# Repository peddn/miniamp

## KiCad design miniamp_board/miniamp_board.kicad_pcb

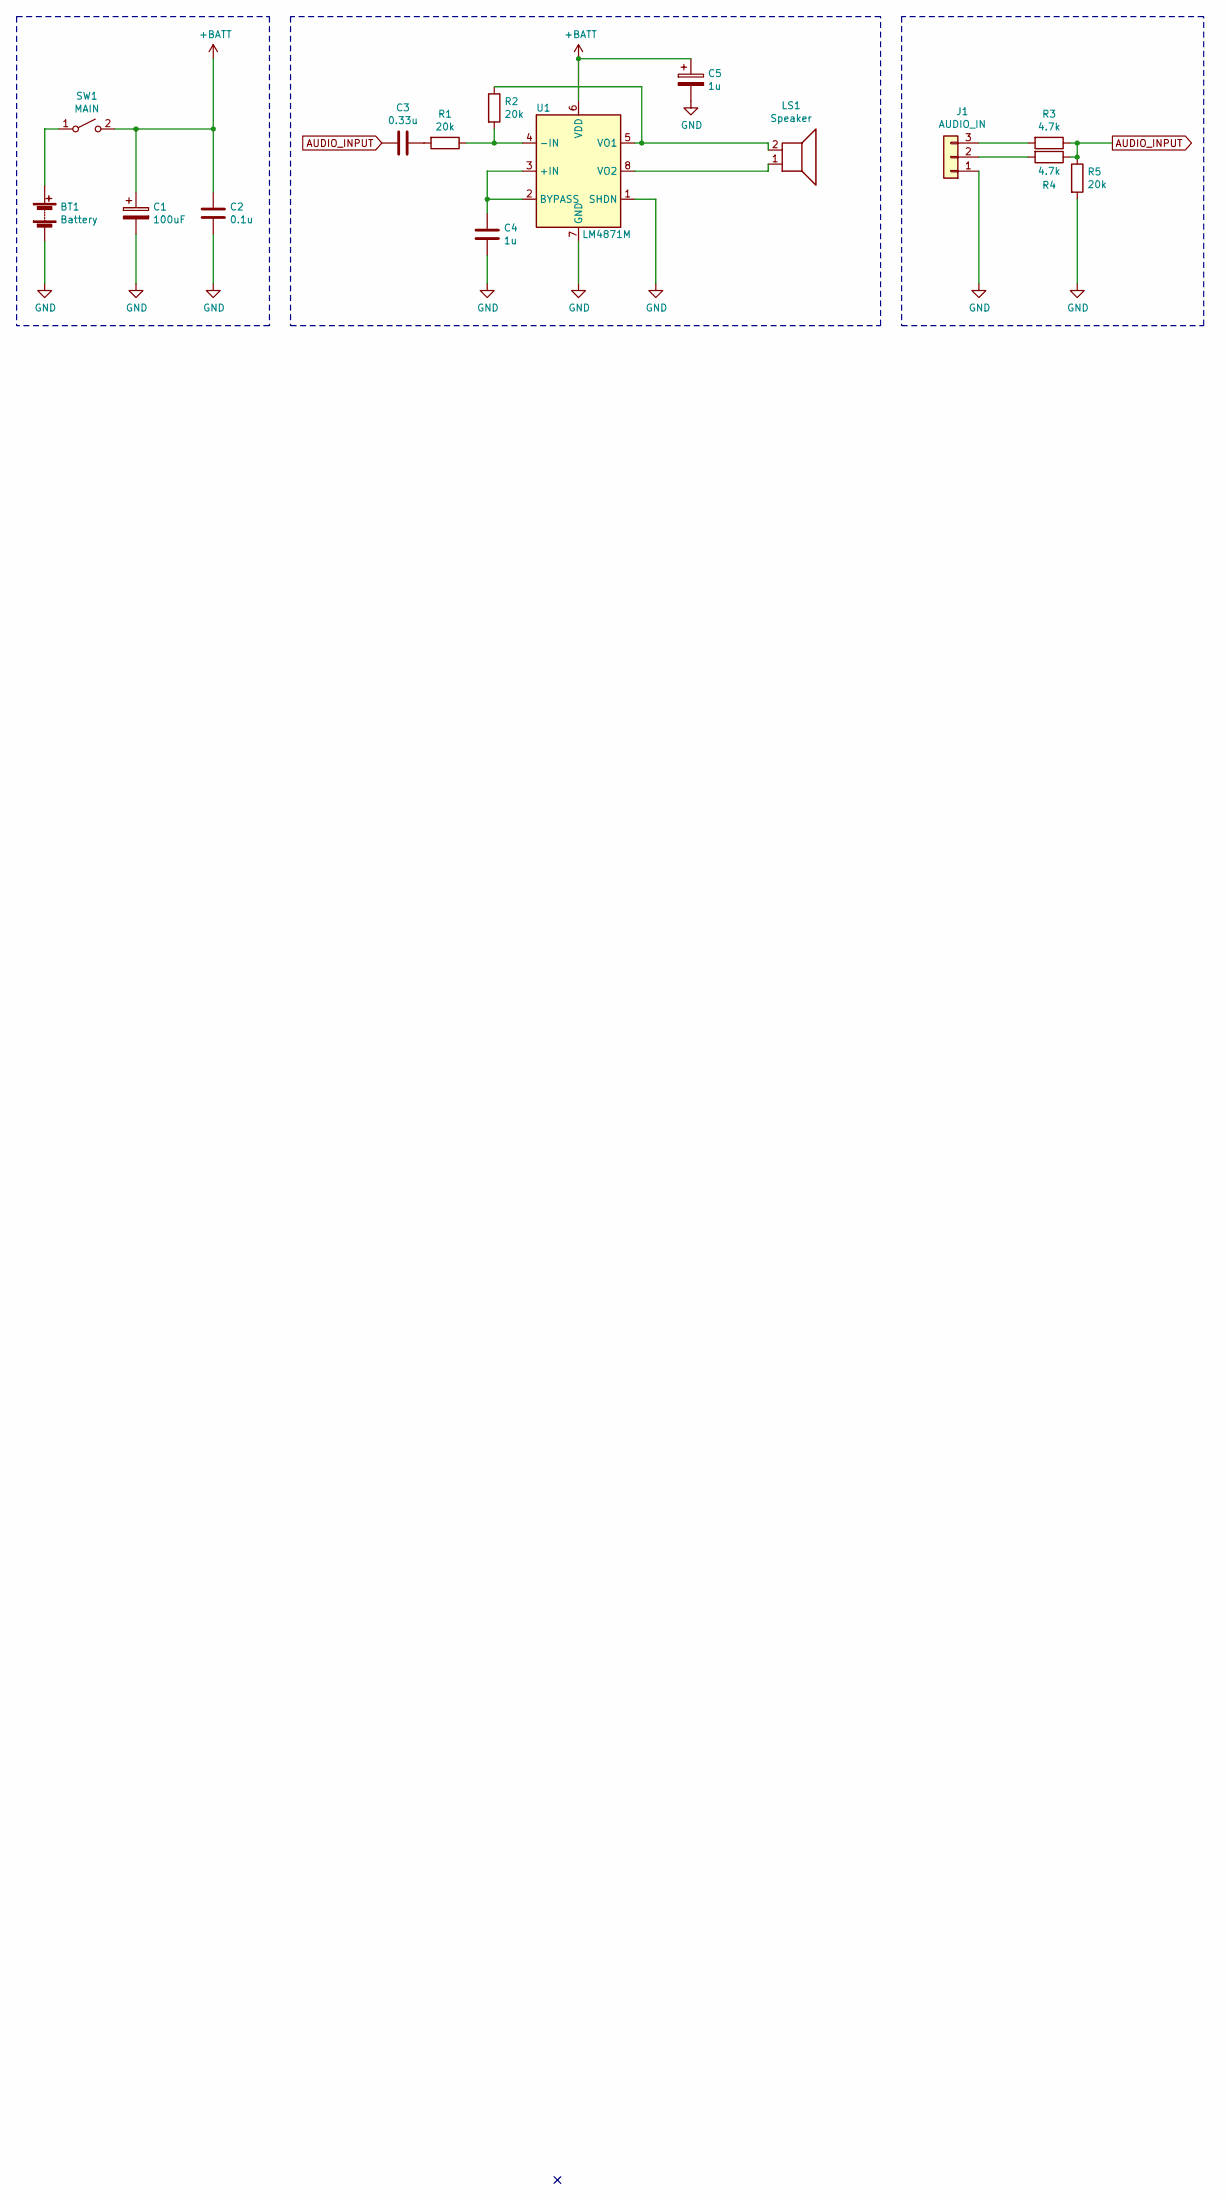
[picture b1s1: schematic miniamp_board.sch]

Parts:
BT1: Battery; JST_XH_S2B-XH-A_1x02_P2.50mm_Horizontal
C1: 100uF; CP_Radial_D6.3mm_P2.50mm
C2: 0.1u; C_Disc_D5.0mm_W2.5mm_P2.50mm
C3: 0.33u; C_Disc_D5.0mm_W2.5mm_P2.50mm
C4: 1u; C_Disc_D5.0mm_W2.5mm_P2.50mm
C5: 1u; CP_Radial_Tantal_D4.5mm_P2.50mm
J1: AUDIO_IN; JST_XH_S3B-XH-A_1x03_P2.50mm_Horizontal
LS1: Speaker; JST_XH_S2B-XH-A_1x02_P2.50mm_Horizontal
R1, R2, R5: 20k; R_Axial_DIN0207_L6.3mm_D2.5mm_P10.16mm_Horizontal
R3, R4: 4.7k; R_Axial_DIN0207_L6.3mm_D2.5mm_P10.16mm_Horizontal
SW1: MAIN; JST_XH_S2B-XH-A_1x02_P2.50mm_Horizontal
U1: LM4871M; SOIC-8_3.9x4.9mm_P1.27mm

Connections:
+BATT: C1.1, C2.1, C5.1, SW1.2 (B), U1.6 (VDD)
AUDIO_INPUT: C3.2, R3.1, R4.1, R5.1
GND: BT1.2 (-), C1.2, C2.2, C4.2, C5.2, J1.1, R5.2, U1.1 (SHDN), U1.7 (GND)
unnamed: BT1.1 (+), SW1.1 (A)
unnamed: C3.1, R1.2
unnamed: C4.1, U1.2 (BYPASS), U1.3 (+IN)
unnamed: J1.2, R4.2
unnamed: J1.3, R3.2
unnamed: LS1.1, U1.8 (VO2)
unnamed: LS1.2, R2.1, U1.5 (VO1)
unnamed: R1.1, R2.2, U1.4 (-IN)

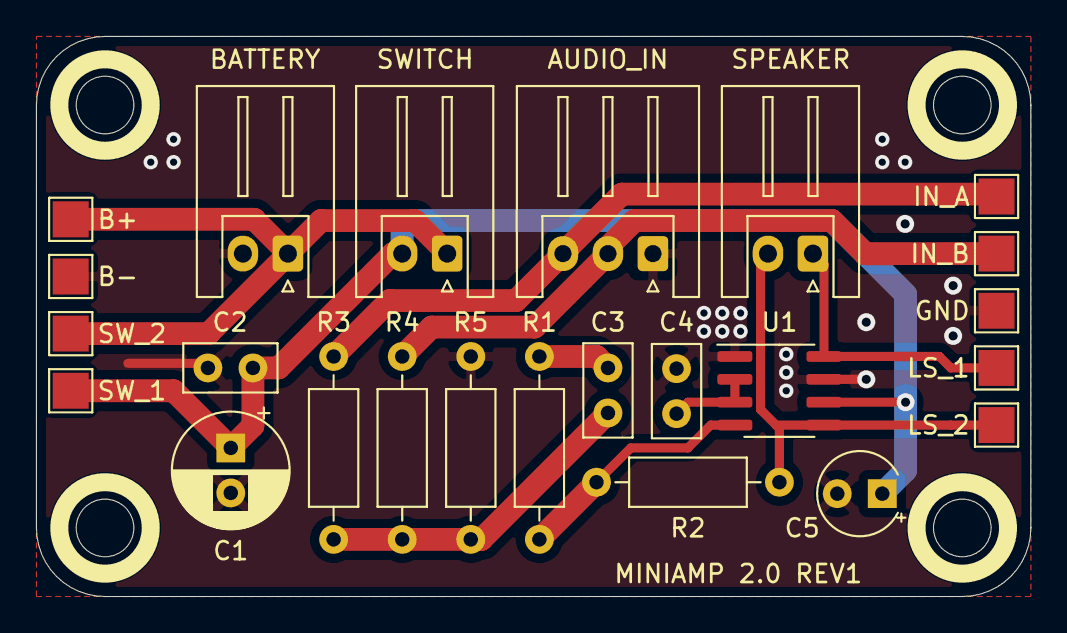
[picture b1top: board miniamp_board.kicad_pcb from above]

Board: 2 copper layers, 55.2 x 31.1 mm, 24 parts (0 on the bottom side), 11 nets.

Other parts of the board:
B+: TestPoint_Pad_2.0x2.0mm
B-: TestPoint_Pad_2.0x2.0mm
GND: TestPoint_Pad_2.0x2.0mm
IN_A: TestPoint_Pad_2.0x2.0mm
IN_B: TestPoint_Pad_2.0x2.0mm
LS_1, LS_2: TestPoint_Pad_2.0x2.0mm
SW_1, SW_2: TestPoint_Pad_2.0x2.0mm

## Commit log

2020-08-19 initial design
